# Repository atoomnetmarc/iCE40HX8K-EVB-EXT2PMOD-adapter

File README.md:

# iCE40HX8K-EVB-EXT to 4 PMOD port adapter.

# Soldering

Solder every SMD component. Measure if 5V gets regulates to 3V3.

Solder every through-hole component. Measure for shorts between any of the signal pins on the tiny 1.27 header J1, correct if needed.

Clean the PCB.

# Pin mapping from PMOD to iCE40HX8K

Header on adapter (J2, J3, J4, J5 column) ➔ pin number on EXT connector (EXT column) ➔ FPGA pin when using EXTx (EXT1, EXT2, EXT3, EXT4 column) connector on FPGA board.

| J2    | EXT   | EXT1  | EXT2  | EXT3  | EXT4  |
| --    | --    | --    | --    | --    | --    |
| 1     | 14    | A7    | K12   | D15   | M5    |
| 2     | 18    | D8    | L13   | F14   | M4    |
| 3     | 22    | F7    | L12   | D16   | N3    |
| 4     | 26    | F9    | M13   | E16   | M3    |
| 7     | 12    | C7    | M16   | F11   | R1    |
| 8     | 16    | B8    | L14   | F12   | P2    |
| 9     | 20    | B9    | N16   | G12   | P1    |
| 10    | 24    | C8    | M14   | G13   | L5    |

| J3    | EXT   | EXT1  | EXT2  | EXT3  | EXT4  |
| --    | --    | --    | --    | --    | --    |
| 1     | 21    | A16   | E6    | K16   | N12   |
| 2     | 17    | E11   | A5    | J15   | M11   |
| 3     | 13    | B14   | A6    | K13   | E13   |
| 4     | 9     | B15   | C6    | J11   | F13   |
| 7     | 19    | C13   | B5    | K15   | T13   |
| 8     | 15    | C12   | D6    | K14   | D14   |
| 9     | 11    | D13   | D7    | L16   | B16   |
| 10    | 7     | C14   | B6    | M15   | C16   |

| J4    | EXT   | EXT1  | EXT2  | EXT3  | EXT4  |
| --    | --    | --    | --    | --    | --    |
| 1     | 35    | B10   | B3    | H16   | L1    |
| 2     | 31    | D11   | C5    | H13   | K3    |
| 3     | 27    | E10   | D5    | J13   | J1    |
| 4     | 23    | A15   | B4    | J14   | M12   |
| 7     | 37    | B11   | D4    | H14   | K4    |
| 8     | 33    | B12   | C4    | H11   | L4    |
| 9     | 29    | C11   | A1    | J16   | K1    |
| 10    | 25    | B13   | A2    | J12   | R16   |

| J5    | EXT   | EXT1  | EXT2  | EXT3  | EXT4  |
| --    | --    | --    | --    | --    | --    |
| 1     | 28    | A9    | P16   | G14   | M6    |
| 2     | 32    | E9    | P14   | G11   | L7    |
| 3     | 36    | D10   | R14   | G10   | K5    |
| 4     | 40    | A10   | D3    | H12   | L6    |
| 7     | 30    | D9    | P15   | F15   | N2    |
| 8     | 34    | C9    | R15   | F16   | M2    |
| 9     | 38    | A11   | C3    | G15   | L3    |
| 10    | 39    | C10   | E5    | G16   | M1    |

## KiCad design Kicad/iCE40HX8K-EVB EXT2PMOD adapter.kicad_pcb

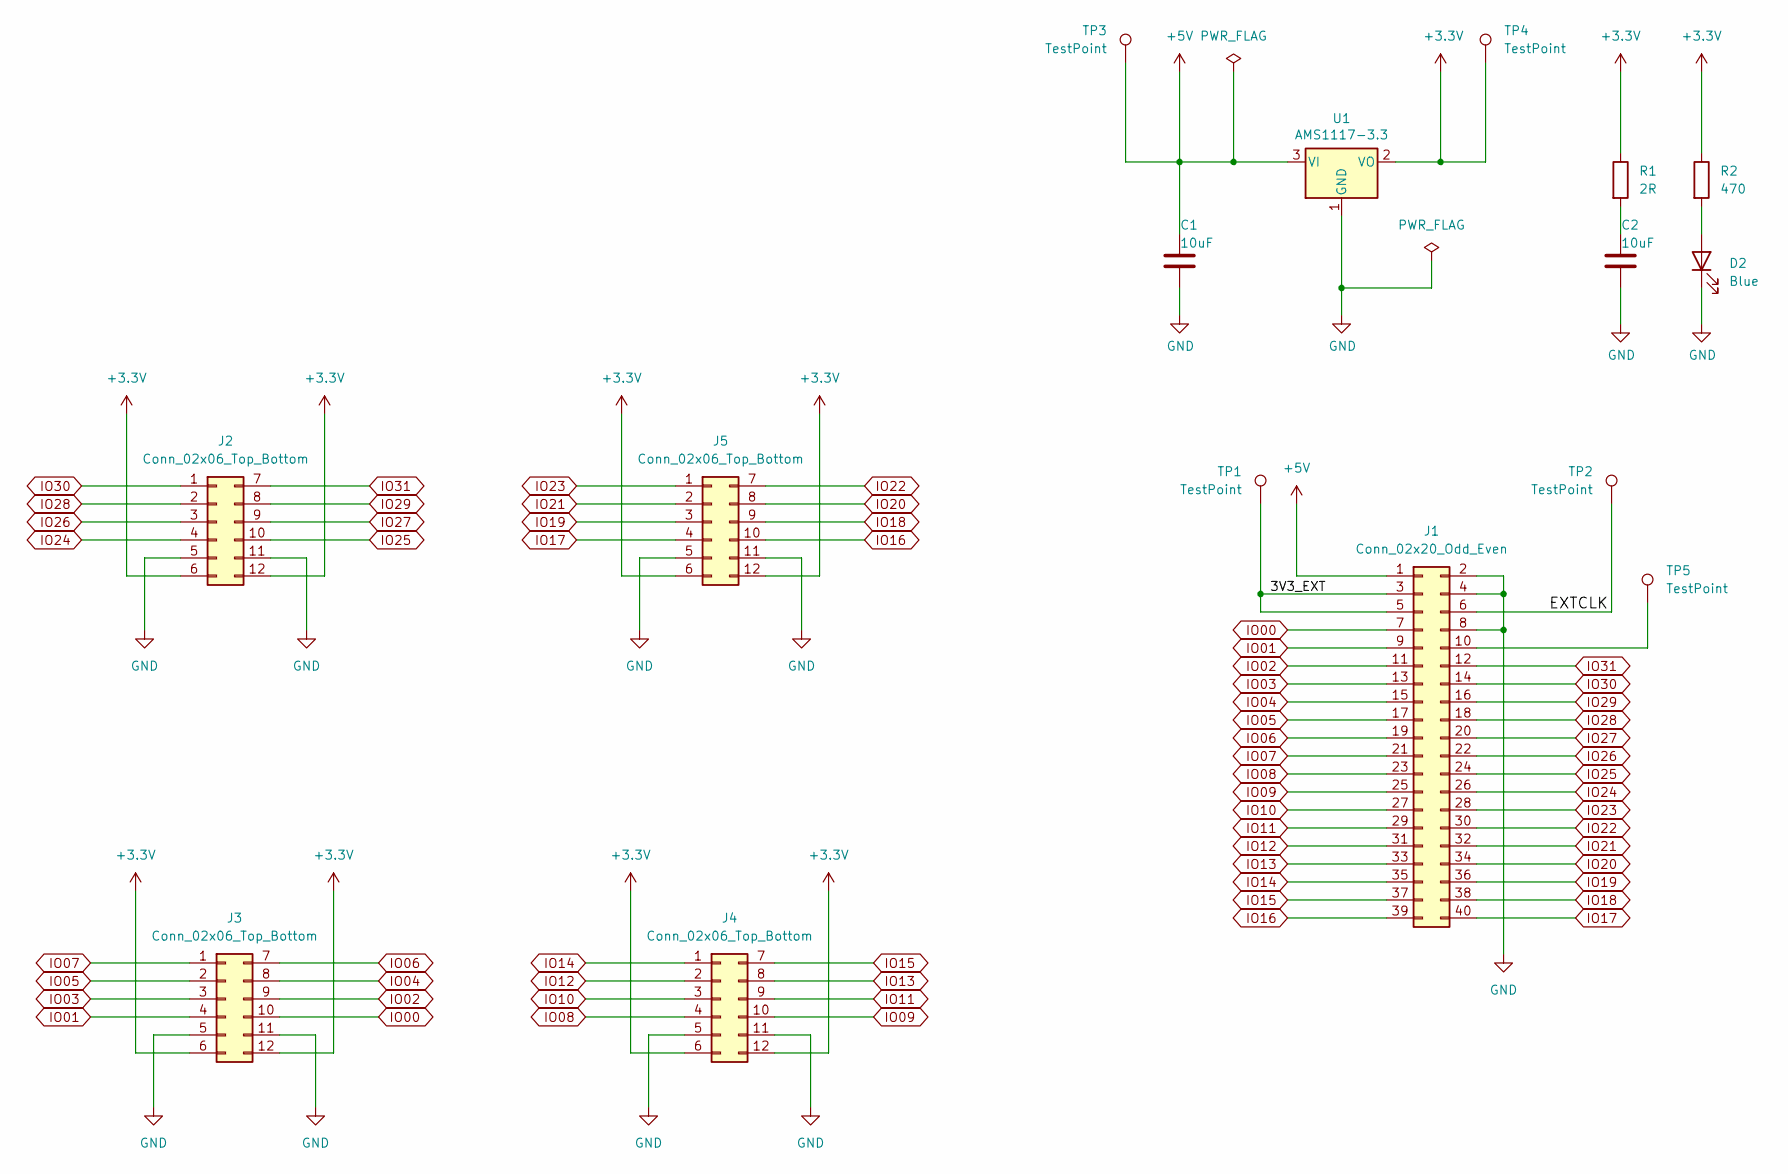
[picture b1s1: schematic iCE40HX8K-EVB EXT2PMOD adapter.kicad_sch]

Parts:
C1, C2: 10uF; C_0805_2012Metric_Pad1.18x1.45mm_HandSolder
D2: Blue; LED_0805_2012Metric_Pad1.15x1.40mm_HandSolder
J1: Conn_02x20_Odd_Even; PinHeader_2x20_P1.27mm_Vertical
J2, J3, J4, J5: Conn_02x06_Top_Bottom; PinSocket_2x06_P2.54mm_Horizontal_Top_Bottom
R1: 2R; R_0805_2012Metric_Pad1.20x1.40mm_HandSolder
R2: 470; R_0805_2012Metric_Pad1.20x1.40mm_HandSolder
TP1, TP2, TP3, TP4: TestPoint; TestPoint_THTPad_2.0x2.0mm_Drill1.0mm
TP5: TestPoint; TestPoint_Pad_D1.5mm
U1: AMS1117-3.3; SOT-223-3_TabPinNC

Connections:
+3.3V: J2.6, J2.12, J3.6, J3.12, J4.6, J4.12, J5.6, J5.12, R1.1, R2.1, TP4.1, U1.2 (VO)
+5V: C1.1, J1.1, TP3.1, U1.3 (VI)
/3V3_EXT: J1.3, J1.5, TP1.1
/EXTCLK: J1.6, TP2.1
GND: C1.2, C2.2, D2.1 (K), J1.2, J1.4, J1.8, J2.5, J2.11, J3.5, J3.11, J4.5, J4.11, J5.5, J5.11, U1.1 (GND)
IO00: J1.7, J3.10
IO01: J1.9, J3.4
IO02: J1.11, J3.9
IO03: J1.13, J3.3
IO04: J1.15, J3.8
IO05: J1.17, J3.2
IO06: J1.19, J3.7
IO07: J1.21, J3.1
IO08: J1.23, J4.4
IO09: J1.25, J4.10
IO10: J1.27, J4.3
IO11: J1.29, J4.9
IO12: J1.31, J4.2
IO13: J1.33, J4.8
IO14: J1.35, J4.1
IO15: J1.37, J4.7
IO16: J1.39, J5.10
IO17: J1.40, J5.4
IO18: J1.38, J5.9
IO19: J1.36, J5.3
IO20: J1.34, J5.8
IO21: J1.32, J5.2
IO22: J1.30, J5.7
IO23: J1.28, J5.1
IO24: J1.26, J2.4
IO25: J1.24, J2.10
IO26: J1.22, J2.3
IO27: J1.20, J2.9
IO28: J1.18, J2.2
IO29: J1.16, J2.8
IO30: J1.14, J2.1
IO31: J1.12, J2.7
unnamed: C2.1, R1.2
unnamed: D2.2 (A), R2.2
unnamed: J1.10, TP5.1

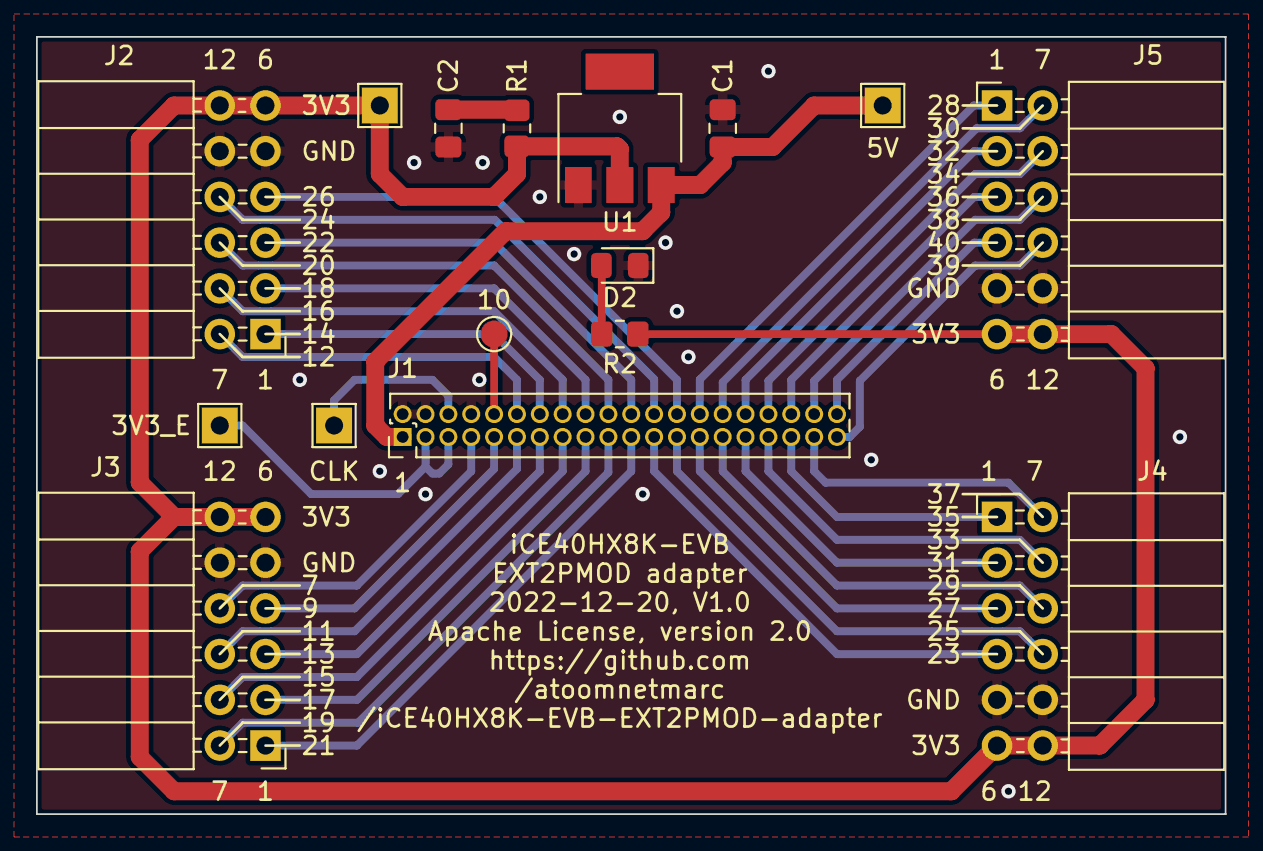
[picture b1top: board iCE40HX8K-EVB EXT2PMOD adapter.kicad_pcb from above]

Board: 2 copper layers, 66.0 x 43.2 mm, 16 parts (0 on the bottom side), 40 nets.

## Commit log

2022-11-20 Initial commit.
2022-11-22 Start adding pin mapping tables.
2022-11-22 Add license badge.
2022-11-29 More pins
2022-12-09 Now with real version.

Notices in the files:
Kicad/iCE40HX8K-EVB EXT2PMOD adapter.kicad_pcb:
Apache License, version 2.0
README.md:
License: Apache 2.0
